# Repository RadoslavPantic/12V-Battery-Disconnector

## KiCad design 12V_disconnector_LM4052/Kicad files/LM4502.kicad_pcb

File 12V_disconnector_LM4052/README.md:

# 12V Battery disconnector

As my first contribution to GitHub, I’m sharing a simple and budget-friendly battery disconnector circuit primarily intended for a 12V Lead-Acid car battery.

The project folder includes:
- `.kicad_pro`, `.kicad_pcb`, and `.kicad_sch` files  
- Gerber files for fabrication
- BOM file

The design is based on the **Texas Instruments LM4052** IC.

The circuit disconnects the battery when the voltage drops below 11.5V. Due to built-in hysteresis, it reconnects only when the voltage goes back up to 12.5V

## Schematic and 3D view

Circuit schematic is shown below:

It uses two Phoenix Contact connectors and two LEDs for indicating when input/output is present.

Only the undervoltage function of the LM4052 is used. As explained in the datasheet, it has fixed hysteresis for the battery voltage. The trigger level is set by a resistor divider connected to the UVLO pin.

There are two NMOS transistors that act as a load switch and also provide reverse polarity protection. The gate driver pin includes inrush current control, which further simplifies the design.

Also included: a 200nF charge pump capacitor, plus input and output electrolytic caps.

The 3D view of the board is shown below:

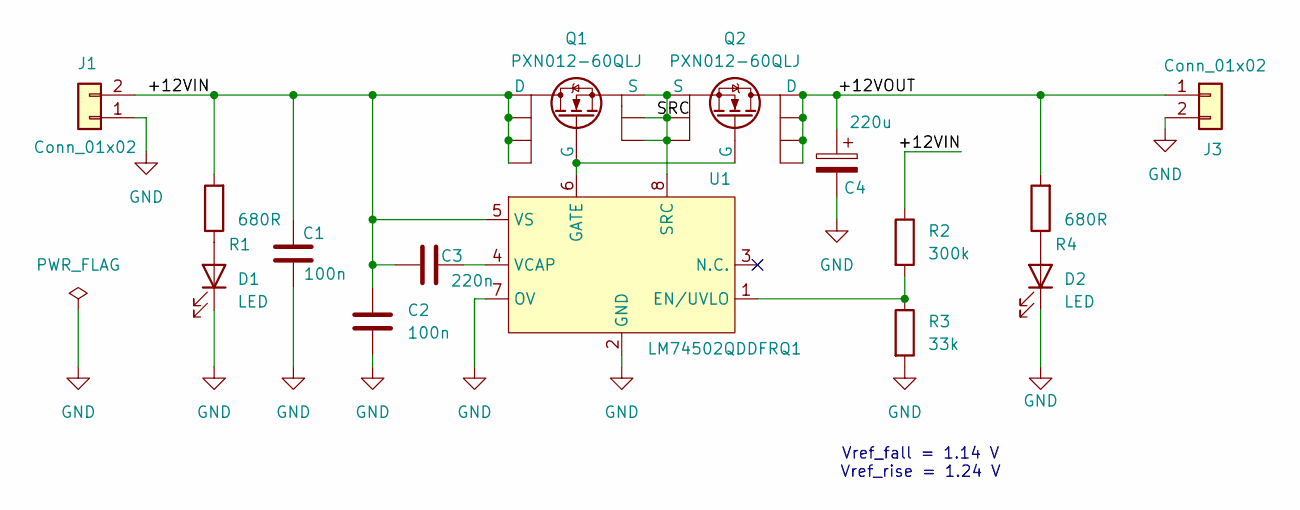
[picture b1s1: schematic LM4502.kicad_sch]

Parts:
C1, C2: 100n; C_0805_2012Metric
C3: 220n; C_0805_2012Metric
C4: 220u; CP_Radial_D6.3mm_P2.50mm
D1, D2: LED; LED_0805_2012Metric
J1, J3: Conn_01x02; PhoenixContact_MC_1,5_2-G-3.81_1x02_P3.81mm_Horizontal
Q1, Q2: PXN012-60QLJ; PXN01260QLJ
R1, R4: 680R; R_0805_2012Metric
R2: 300k; R_0805_2012Metric
R3: 33k; R_0805_2012Metric
U1: LM74502QDDFRQ1; SOT-23-8

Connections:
/+12VIN: C1.2, C2.1, C3.1, J1.2, Q1.5 (D), Q1.6, Q1.7, Q1.8, R1.2, R2.1, U1.5 (VS)
/+12VOUT: C4.1, J3.1, Q2.5 (D), Q2.6, Q2.7, Q2.8, R4.2
/SRC: Q1.1, Q1.2, Q1.3 (S), Q2.1, Q2.2, Q2.3 (S), U1.8 (SRC)
GND: C1.1, C2.2, C4.2, D1.1 (K), D2.1 (K), J1.1, J3.2, R3.2, U1.2 (GND), U1.7 (OV)
unnamed: D1.2 (A), R1.1
unnamed: D2.2 (A), R4.1
unnamed: Q1.4 (G), Q2.4 (G), U1.6 (GATE)
unnamed: R2.2, R3.1, U1.1 (EN/UVLO)
unnamed: C3.2, U1.4 (VCAP)

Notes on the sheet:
Vref_fall = 1.14 V Vref_rise = 1.24 V

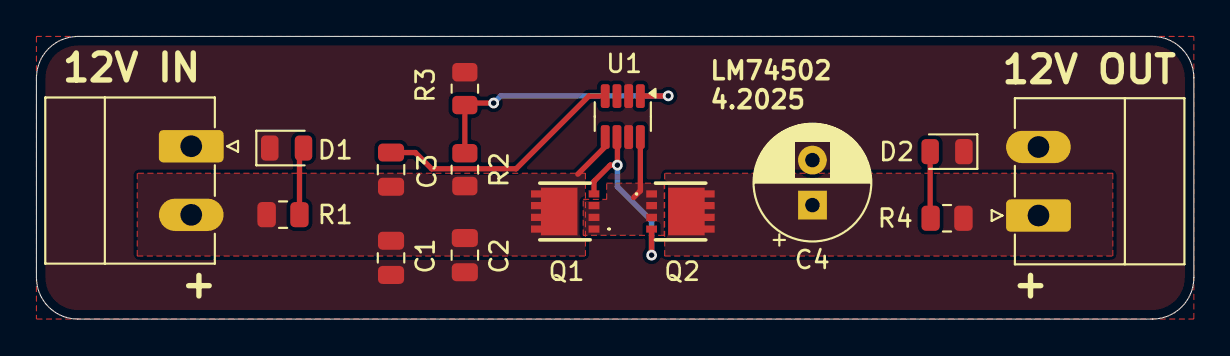
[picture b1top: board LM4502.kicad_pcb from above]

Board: 2 copper layers, 64.3 x 15.7 mm, 15 parts (0 on the bottom side), 9 nets.

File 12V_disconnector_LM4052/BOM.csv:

Reference,Qty,Value,Footprint,Datasheet
"C1,C2",2,100n,Capacitor_SMD:C_0805_2012Metric,~
C3,1,220n,Capacitor_SMD:C_0805_2012Metric,~
C4,1,220u,Capacitor_THT:CP_Radial_D6.3mm_P2.50mm,https://www.we-online.com/components/products/datasheet/8600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
"D1,D2",2,LED,LED_SMD:LED_0805_2012Metric,~
"J1,J3",2,Conn_01x02,"Connector_Phoenix_MC:PhoenixContact_MC_1,5_2-G-3.81_1x02_P3.81mm_Horizontal",~
"Q1,Q2",2,PXN012-60QLJ,PXN012-60QLJ:PXN01260QLJ,https://assets.nexperia.com/documents/data-sheet/PXN012-60QL.pdf
"R1,R4",2,680R,Resistor_SMD:R_0805_2012Metric,~
R2,1,300k,Resistor_SMD:R_0805_2012Metric,~
R3,1,33k,Resistor_SMD:R_0805_2012Metric,~
U1,1,LM74502QDDFRQ1,Package_TO_SOT_SMD:SOT-23-8,https://www.ti.com/lit/ds/symlink/lm74502-q1.pdf?ts=17448746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

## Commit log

2025-05-14 Add files via upload
    initial upload
